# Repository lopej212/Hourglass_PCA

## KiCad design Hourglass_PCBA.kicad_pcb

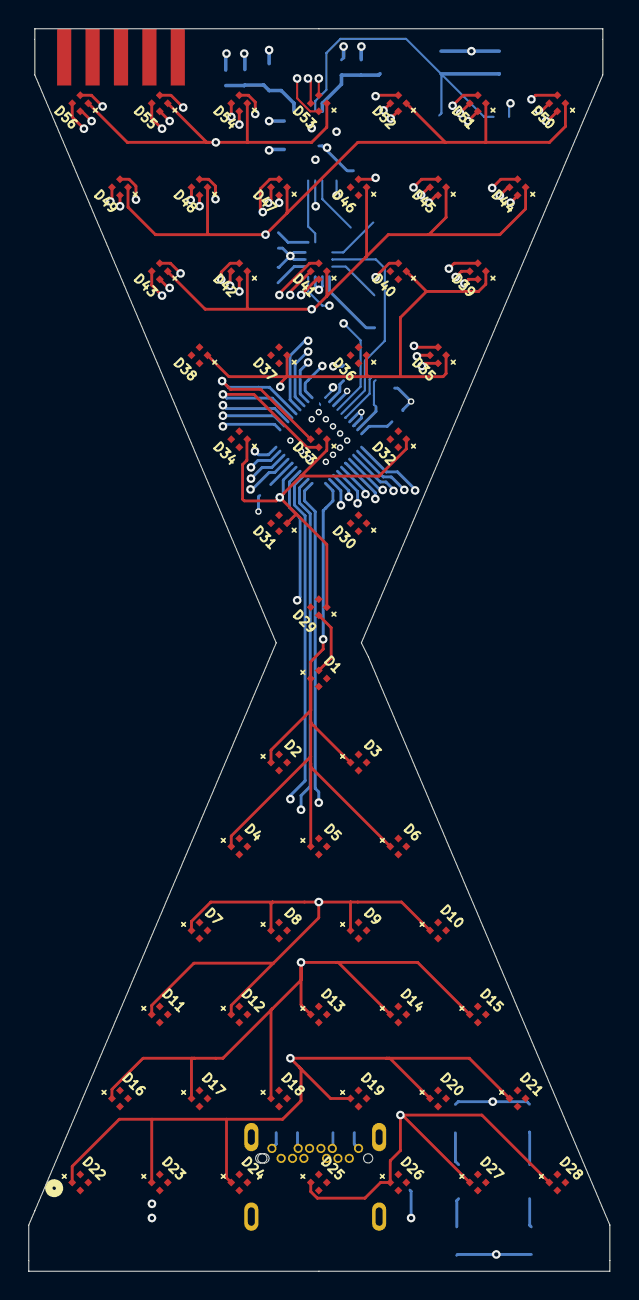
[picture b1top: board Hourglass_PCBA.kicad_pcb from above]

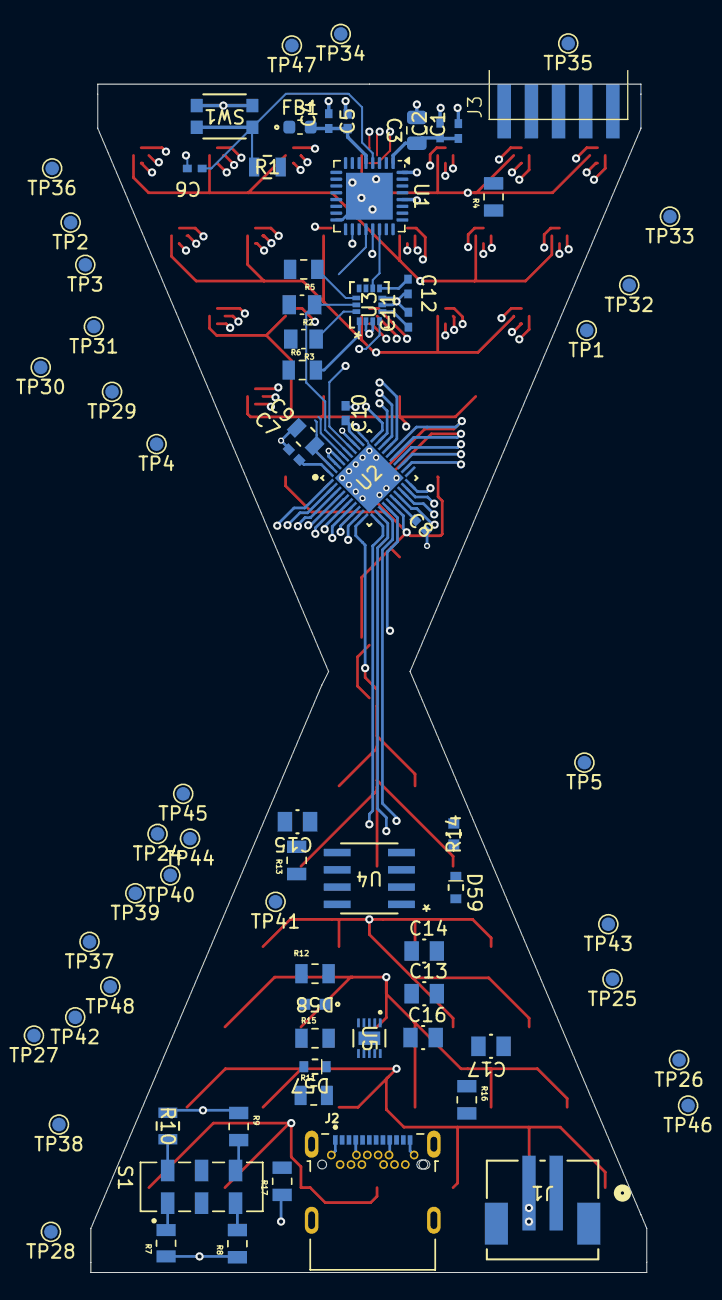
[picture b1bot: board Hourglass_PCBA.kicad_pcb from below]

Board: 4 copper layers, 40.9 x 87.5 mm, 134 parts (78 on the bottom side), 64 nets.

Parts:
C1, C2, C4, C6, C11, C12: CC0402KRX7R6BB104; YAG_CC0402_YAG
C3: GRM21BR71A475KE51L
C5, C7, C8, C10: GRM155Z71A105KE01D; CAP_GRM155Z_MUR
C9: SH05B102K251DC; CAP_CL21_SAM
C13, C14, C15, C16, C17: GRM21BZ71E106KE15L; CAP_GRM21BZ_MUR
D1, D2, D3, D4, D5, D6, D7, D8, D9, D10, D11, D12, D13, D14, D15, D16, D17, D18, D19, D20, D21, D22, D23, D24, D25, D26, D27, D28, D29, D30, D31, D32, D33, D34, D35, D36, D37, D38, D39, D40, D41, D42, D43, D44, D45, D46, D47, D48, D49, D50, D51, D52, D53, D54, D55, D56: 150044M155220
D57: LTST-C193KRKT-5A; LED_LTST-C193KGKT-5A_LTO
D58: LTST-C193TBKT-5A
D59: LTST-C193KGKT-5A; LED_LTST-C193KGKT-5A_LTO
FB1: FCM 1608KF-601T03; FB_0603_1608Metric
J1: B2B-PH-SM4-TBLFSN; CONN_B2B-PH-SM4-TBLFSN_JST
J2: UJ31-CH-G2-SMT-TR; CUI_UJ31-CH-G2-SMT-TR
J3: 009159010061911
R1, R10: CRCW080518K0FKEAHP
R2, R3: CRGCQ0805F4K7
R4, R5, R6, R13, R15: RMCF0805FT10K0
R7, R11: MCU08050C6000FP500; RESC2012X55N
R8: RCS0805300RFKEA
R9: RCS080513K0FKEA
R12: RC0805FR-07442RL
R14: RC0603JR-07300RL; RC0603N_YAG
R16, R17: RC0805FR-075K1L
S1: JS202011JCQN
SW1: KMR221NGLFS; KMR221_CNK
TP1, TP2, TP3, TP4, TP5, TP24, TP25, TP26, TP27, TP28, TP29, TP30, TP31, TP32, TP33, TP34, TP35, TP36, TP37, TP38, TP39, TP40, TP41, TP42, TP43, TP44, TP45, TP46, TP47, TP48: TestPoint; TestPoint_Pad_D1.0mm
U1: STM32L432KCUx; QFN-32-1EP_5x5mm_P0.5mm_EP3.45x3.45mm
U2: LP5860
U3: LSM6DSOXTR; LSM6DSOX
U4: MCP1727T-3302E/SN; MCP1727T-3302E_SN
U5: BQ25185DLHR; BQ25185

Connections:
+3V3: C1.1, C2.1, C3.1, C7.1, C8.1, C11.1, C12.1, C15.1, FB1.1, J3.10, R1.2, R2.2, R3.2, R5.2, R13.2, R14.2, TP40.1, U1.1 (VDD), U1.17 (VDD), U2.16 (VLED), U2.40 (VCC), U3.5 (VDDIO), U3.8 (VDD), U4.7 (SENSE), U4.8 (VOUT)
/LED Driver + LEDs/CS0: D1.2, D7.2, D13.2, D19.2, D25.2, D29.2, D35.2, D41.2, D47.2, D53.2, U2.1 (CS0)
/LED Driver + LEDs/CS1: D1.3, D7.3, D13.3, D19.3, D25.3, D29.3, D35.3, D41.3, D47.3, D53.3, U2.2 (CS1)
/LED Driver + LEDs/CS2: D1.4, D7.4, D13.4, D19.4, D25.4, D29.4, D35.4, D41.4, D47.4, D53.4, U2.3 (CS2)
/LED Driver + LEDs/CS3: D2.2, D8.2, D14.2, D20.2, D26.2, D30.2, D36.2, D42.2, D48.2, D54.2, U2.4 (CS3)
/LED Driver + LEDs/CS4: D2.3, D8.3, D14.3, D20.3, D26.3, D30.3, D36.3, D42.3, D48.3, D54.3, U2.5 (CS4)
/LED Driver + LEDs/CS5: D2.4, D8.4, D14.4, D20.4, D26.4, D30.4, D36.4, D42.4, D48.4, D54.4, U2.6 (CS5)
/LED Driver + LEDs/CS6: D3.2, D9.2, D15.2, D21.2, D27.2, D31.2, D37.2, D43.2, D49.2, D55.2, U2.7 (CS6)
/LED Driver + LEDs/CS7: D3.3, D9.3, D15.3, D21.3, D27.3, D31.3, D37.3, D43.3, D49.3, D55.3, U2.8 (CS7)
/LED Driver + LEDs/CS8: D3.4, D9.4, D15.4, D21.4, D27.4, D31.4, D37.4, D43.4, D49.4, D55.4, U2.9 (CS8)
/LED Driver + LEDs/CS9: D4.2, D10.2, D16.2, D22.2, D28.2, D32.2, D38.2, D44.2, D50.2, D56.2, U2.22 (CS9)
/LED Driver + LEDs/CS10: D4.3, D10.3, D16.3, D22.3, D28.3, D32.3, D38.3, D44.3, D50.3, D56.3, U2.23 (CS10)
/LED Driver + LEDs/CS11: D4.4, D10.4, D16.4, D22.4, D28.4, D32.4, D38.4, D44.4, D50.4, D56.4, U2.24 (CS11)
/LED Driver + LEDs/CS12: D5.2, D11.2, D17.2, D23.2, D33.2, D39.2, D45.2, D51.2, U2.25 (CS12)
/LED Driver + LEDs/CS13: D5.3, D11.3, D17.3, D23.3, D33.3, D39.3, D45.3, D51.3, U2.26 (CS13)
/LED Driver + LEDs/CS14: D5.4, D11.4, D17.4, D23.4, D33.4, D39.4, D45.4, D51.4, U2.27 (CS14)
/LED Driver + LEDs/CS15: D6.2, D12.2, D18.2, D24.2, D34.2, D40.2, D46.2, D52.2, U2.28 (CS15)
/LED Driver + LEDs/CS16: D6.3, D12.3, D18.3, D24.3, D34.3, D40.3, D46.3, D52.3, U2.29 (CS16)
/LED Driver + LEDs/CS17: D6.4, D12.4, D18.4, D24.4, D34.4, D40.4, D46.4, D52.4, U2.30 (CS17)
/LED Driver + LEDs/I2C.SCL: R2.1, TP3.1, U1.19 (PA9), U2.35 (SCL_SCLK), U3.13 (SCL)
/LED Driver + LEDs/I2C.SDA: R3.1, TP4.1, U1.20 (PA10), U2.36 (SDA_MOSI), U3.14 (SDA)
/LED Driver + LEDs/SW0: D1.1, D2.1, D3.1, D4.1, D5.1, D6.1, TP24.1, U2.10 (SW0)
/LED Driver + LEDs/SW1: D7.1, D8.1, D9.1, D10.1, D11.1, D12.1, TP25.1, U2.11 (SW1)
/LED Driver + LEDs/SW2: D13.1, D14.1, D15.1, D16.1, D17.1, D18.1, TP26.1, U2.12 (SW2)
/LED Driver + LEDs/SW3: D19.1, D20.1, D21.1, D22.1, D23.1, D24.1, TP27.1, U2.13 (SW3)
/LED Driver + LEDs/SW4: D25.1, D26.1, D27.1, D28.1, TP28.1, U2.14 (SW4)
/LED Driver + LEDs/SW5: D29.1, D30.1, D31.1, D32.1, D33.1, D34.1, TP29.1, U2.15 (SW5)
/LED Driver + LEDs/SW6: D35.1, D36.1, D37.1, D38.1, D39.1, D40.1, TP30.1, U2.17 (SW6)
/LED Driver + LEDs/SW7: D41.1, D42.1, D43.1, D44.1, D45.1, D46.1, TP31.1, U2.18 (SW7)
/LED Driver + LEDs/SW8: D47.1, D48.1, D49.1, D50.1, D51.1, D52.1, TP32.1, U2.19 (SW8)
/LED Driver + LEDs/SW9: D53.1, D54.1, D55.1, D56.1, TP33.1, U2.20 (SW9)
/LED Driver + LEDs/VIO_EN: C9.1, TP5.1, U1.28 (PB5), U2.39 (VIO_EN)
/LED Driver + LEDs/VSYNC: TP2.1, U1.18 (PA8), U2.34 (VSYNC)
/LSM6DSOX 6-Axis IMU/LSM6DSOX_INT1: TP35.1, U1.21 (PA11), U3.4 (INT1)
/LSM6DSOX 6-Axis IMU/LSM6DSOX_INT2: TP34.1, U1.22 (PA12), U3.9 (INT2)
/MCU/BOOT: R4.2, U1.31 (PH3)
/MCU/NRST: C6.1, J3.9, R1.1, SW1.1, SW1.4, U1.4 (NRST)
/MCU/RX: J3.7, U1.25 (PA15)
/MCU/SWCLK: J3.4, U1.24 (PA14)
/MCU/SWDIO: J3.3, U1.23 (PA13)
/MCU/TX: J3.8, U1.8 (PA2)
/Power/ILIM/VSET: S1.6, TP41.1, U5.7 (ILIM/VSET)
/Power/ISET: S1.2, TP43.1, U5.8 (ISET)
GND: C1.2, C2.2, C3.2, C4.2, C5.2, C6.2, C7.2, C8.2, C9.2, C10.2, C11.2, C12.2, C13.2, C14.2, C15.2, C16.2, C17.2, D59.2, J1.2, J2.A1 (GND), J2.A12 (GND__1), J2.B1 (GND__2), J2.B12 (GND__3), J2.SH1 (SHIELD), J2.SH2 (SHIELD__1), J2.SH3 (SHIELD__2), J2.SH4 (SHIELD__3), J3.6, R4.1, R6.1, R7.1, R8.1, R9.1, R10.1, R15.1, R16.1, R17.1, SW1.2, SW1.3, TP45.1, TP46.1, TP47.1, TP48.1, U1.16 (VSS), U1.32 (VSS), U1.33 (VSS), U2.31 (AGND), U2.33 (IFS), U2.37 (ADDR0_MISO), U2.38 (ADDR1_SS), U2.41 (GND), U3.2 (SDX), U3.3 (SCX), U3.6 (GND), U3.7 (GND), U4.4 (GND), U5.4 (/CE), U5.5 (GND), U5.11 (EPAD)
unnamed: D57.2, R11.1
unnamed: D58.2, R12.1
unnamed: D59.1, R14.1
unnamed: J2.A5 (CC1), R17.2
unnamed: J2.B5 (CC2), R16.2
unnamed: R7.2, S1.1
unnamed: R8.2, S1.3
unnamed: R9.2, S1.7
unnamed: R10.2, S1.5
unnamed: C10.1, U2.32 (VCAP)
unnamed: R5.1, TP36.1, U3.12 (CS)
unnamed: R6.2, U3.1 (SDO/SA0)
unnamed: C13.1, C14.1, TP42.1, U4.1 (VIN), U4.2 (VIN), U4.3 (*SHDN), U5.1 (SYS)
unnamed: R13.1, U4.5 (PWRGD)
unnamed: C17.1, J1.1, TP44.1, U5.2 (BAT)
unnamed: D57.1, TP38.1, U5.9 (STAT1)
unnamed: D58.1, TP39.1, U5.3 (STAT2)
unnamed: R15.2, U5.6 (TS/MR)
VCC: C16.1, J2.A4 (VBUS), J2.A9 (VBUS__1), J2.B4 (VBUS__2), J2.B9 (VBUS__3), R11.2, R12.2, TP37.1, U5.10 (IN)
VDDA: C4.1, C5.1, FB1.2, TP1.1, U1.5 (VDDA)

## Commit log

2025-02-03 Removing backups. Adding gitignore
2025-02-03 Progress commit. Added MCU + IMU.
2025-03-19 Finished power section.
2025-03-19 Minor update
2025-03-20 Finished LSM6DSOX schematic
2025-03-21 Initial complete implementation of LEDS.
2025-03-21 Removed unused files.
2025-03-27 Completed schematic for MCU section
2025-04-03 First complete schematic with TPs.
2025-04-04 Addressed DRC warnings and errors.
2025-04-04 Added exclusion and footprint.
2025-04-04 Updated PCB layout parts.
2025-04-10 Saving project progress.
2025-04-10 Added comments on schematic and fixed bus for SW[0..4] on Bot LEDs.
2025-04-20 Addressed pull-up on NRST. Added GPIO for VIO_EN. Added comments on schematic and some TPs
2025-04-20 No need to track backup file.
2025-04-24 Changed PUs for I2C and added TPs.
2025-04-24 Updated addressing comment for LSM6DSOXTR and added ref image.
2025-04-24 Re-annotated entire schematic.
2025-04-24 Fixed ERC Errors.
2025-04-24 Updated gitignore to stop tracking temp cache file.
2025-05-30 Added comment regarding push-pull default for INT1 and INT2
2025-07-02 Aligned all LEDs
2025-07-09 Arranged parts for power- not complete at this commit.
2025-07-17 Moved all TPs to board area except CS TPs. Deleted some TPs that are less of a priority.
2025-07-18 Updated the 3D models
2025-07-22 Started routing all of the SW sides.
2025-08-07 Routed all of the SWx nets. Routing the CSx.
2025-09-30 Progress commit
